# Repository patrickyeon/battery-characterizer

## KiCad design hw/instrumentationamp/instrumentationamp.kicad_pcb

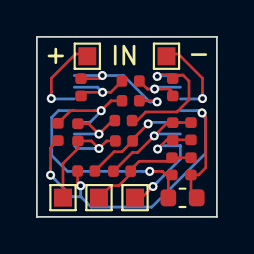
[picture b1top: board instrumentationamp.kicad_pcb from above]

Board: 2 copper layers, 10.0 x 10.0 mm, 21 parts (1 on the bottom side), 15 nets.

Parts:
C1: 100n; C_0603_1608Metric
C2: 10n; C_0402_1005Metric
R1, R4, R5, R11: 1K; R_0402_1005Metric
R2, R3: 2K; R_0402_1005Metric
R6, R7: 10K; R_0402_1005Metric
R8: DNI; R_0402_1005Metric
R9: 1M; R_0402_1005Metric
R10: 1k; R_0402_1005Metric
R12, R13: 250k; R_0402_1005Metric
TP1, TP2, TP3, TP4, TP7: Test_Point; TestPoint_Pad_1.0x1.0mm
U1: TLV274; TSSOP-14_4.4x5mm_P0.65mm

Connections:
/Vimeas: R7.1, R11.2, TP4.1, U1.1
/Vin+: TP2.1, U1.5
/Vin-: TP1.1, U1.10
/Viset: R8.1, R9.2, R10.1, TP3.1
/vout: C2.1, R13.1, TP7.1, U1.14
GND: C1.2, R6.2, R9.1, R12.1, U1.11
unnamed: C2.2, R10.2, R13.2, U1.13
unnamed: R1.1, R2.1, U1.9
unnamed: R1.2, R3.2, U1.6
unnamed: R2.2, R4.2, U1.8
unnamed: R3.1, R5.2, U1.7
unnamed: R4.1, R7.2, U1.2
unnamed: R5.1, R6.1, U1.3
unnamed: R11.1, R12.2, U1.12
VCC: C1.1, R8.2, U1.4

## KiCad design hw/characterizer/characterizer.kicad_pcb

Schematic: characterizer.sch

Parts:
C1: 1u; C_0603_1608Metric
C2: 470p; C_0603_1608Metric
C3: 2u2; C_0603_1608Metric
J1: 1988820; TERM_4_5mm; Digikey PN 277-1766-ND
R1: 0R; R_0603_1608Metric
R2: DNI; R_0603_1608Metric
R3, R4, R5: 10k; R_0603_1608Metric
U1: MIC5205-3.3; SOT-23-5; Digikey PN 576-1259-1-ND

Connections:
+3V3: C3.1, R5.1, U1.5 (OUT); also elsewhere on the board
+5V: R2.1; also elsewhere on the board
+6V: J1.1, J1.2, R1.1; also elsewhere on the board
/pairA/ADDR: R4.1; also elsewhere on the board
/pairB/ADDR: R5.2; also elsewhere on the board
GND: C1.2, C2.2, C3.2, J1.3, J1.4, R4.2, U1.2 (GND); also elsewhere on the board
unnamed: C1.1, R1.2, R2.2, R3.1, U1.1 (IN)
unnamed: C2.1, U1.4 (BP)
unnamed: R3.2, U1.3 (EN)

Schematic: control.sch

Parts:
C4: 4n7; C_0603_1608Metric
C5, C7, C9, C10, C11, C12, C13, C14: 100n; C_0603_1608Metric
C6, C8: 18p; C_0603_1608Metric
J2: Conn_02x05_Odd_Even; CONN_JTAG_10; Digikey PN 1175-1629-ND
J3: 10118194-0001LF; USB-microB-AMPH; Digikey PN 609-4618-1-ND
R6: 1M; R_0603_1608Metric
R7: DNI; R_0603_1608Metric
R8, R13, R14, R15, R16, R19, R20, R21, R22: 10k; R_0603_1608Metric
R9: 100k; R_0603_1608Metric
R10: 0; R_0603_1608Metric
R11, R12: 3k3; R_0603_1608Metric
R17, R18, R23, R24: 4k02; R_0603_1608Metric
U2: STM32F042K6T6; LQFP-32_7x7mm_P0.8mm; Digikey PN 497-14647-ND
U3: 74LVC2G04GW,125; SOT-363_SC-70-6; Digikey PN 1727-4032-1-ND
Y1: ABLS-8.000MHZ-B4-T; Crystal_SMD_HC49-SD; Digikey PN 535-10212-1-ND

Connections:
+3V3: C5.1, C7.1, C9.1, C10.1, J2.1, R7.1, R11.2, R12.2, U2.1, U2.5, U2.17, U3.5; also elsewhere on the board
+5V: R10.1; also elsewhere on the board
/SCL: R12.1, U2.19; also elsewhere on the board
/SDA: R11.1, U2.20; also elsewhere on the board
/mcu/CC_A: U2.6; also elsewhere on the board
/mcu/CC_B: U2.7; also elsewhere on the board
/mcu/CEN_A: U2.29; also elsewhere on the board
/mcu/CEN_B: U2.25; also elsewhere on the board
/mcu/DC_A: U2.8; also elsewhere on the board
/mcu/DC_B: U2.9; also elsewhere on the board
/mcu/ICHG_A: C14.1, R24.1; also elsewhere on the board
/mcu/ICHG_B: C12.1, R18.1; also elsewhere on the board
/mcu/IDCHG_A: C13.1, R23.1; also elsewhere on the board
/mcu/IDCHG_B: C11.1, R17.1; also elsewhere on the board
/mcu/VBAT0: R15.1; also elsewhere on the board
/mcu/VBAT1: R21.1; also elsewhere on the board
/mcu/VBAT2: R16.1; also elsewhere on the board
/mcu/VBAT3: R22.1; also elsewhere on the board
/pairA/DCHARGE: U2.30; also elsewhere on the board
/pairA/DIR: U2.18, U3.3; also elsewhere on the board
/pairA/nDIR: U3.4; also elsewhere on the board
/pairB/DCHARGE: R7.2, R8.1, U2.31; also elsewhere on the board
/pairB/DIR: U2.26, U3.1; also elsewhere on the board
/pairB/nDIR: U3.6; also elsewhere on the board
GND: C4.2, C5.2, C6.2, C7.2, C8.2, C9.2, C10.2, C11.2, C12.2, C13.2, C14.2, J2.3, J2.5, J2.9, J3.5, R6.1, R8.2, R9.1, R13.2, R14.2, R19.2, R20.2, U2.16, U2.32, U3.2; also elsewhere on the board
unnamed: C4.1, J3.6, J3.7, J3.8, J3.9, R6.2
unnamed: C6.1, U2.2, Y1.1
unnamed: C8.1, U2.3, Y1.2
unnamed: J2.2, U2.23
unnamed: J2.4, U2.24
unnamed: J2.10, U2.4
unnamed: J3.1, R10.2
unnamed: J3.2, U2.21
unnamed: J3.3, U2.22
unnamed: J3.4, R9.2
unnamed: R13.1, R15.2, U2.11
unnamed: R14.1, R16.2, U2.13
unnamed: R17.2, U2.15
unnamed: R18.2, U2.28
unnamed: R19.1, R21.2, U2.10
unnamed: R20.1, R22.2, U2.12
unnamed: R23.2, U2.14
unnamed: R24.2, U2.27

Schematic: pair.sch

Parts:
BT1, BT2: Battery_Cell; 18650-keyelco
C15, C16: 100n; C_0603_1608Metric
F1, F2: MF-USML700-2; R_1210_3225Metric; Digikey PN MF-USML700-2CT-ND
J4, J5, J6, J7: 36-54-ND; BATTERY_CLIP_36-54; Digikey PN 36-54-ND
R25, R26, R27, R28: 10k; R_0603_1608Metric
U4, U5: AT30TS74; MSOP-8_3x3mm_P0.65mm; Digikey PN 1611-AT30TS74-XM8M-B-ND

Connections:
+3V3: C15.1, C16.1, R26.1, U4.8, U5.8; also elsewhere on the board
/SCL: U4.2, U5.2; also elsewhere on the board
/SDA: U4.1, U5.1; also elsewhere on the board
/mcu/VBAT2: J4.1, J4.2, J4.3; also elsewhere on the board
/mcu/VBAT3: J6.1, J6.2, J6.3; also elsewhere on the board
/pairB/ADDR: U4.5, U5.5; also elsewhere on the board
GND: C15.2, C16.2, F1.2, F2.2, R25.2, R27.2, R28.2, U4.4, U5.4; also elsewhere on the board
unnamed: F1.1, J5.1, J5.2, J5.3
unnamed: F2.1, J7.1, J7.2, J7.3
unnamed: R25.1, U4.7
unnamed: R26.2, U5.7
unnamed: R27.1, U4.6
unnamed: R28.1, U5.6

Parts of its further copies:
BT3, BT4: Battery_Cell; 18650-keyelco
C32, C33: 100n; C_0603_1608Metric
F3, F4: MF-USML700-2; R_1210_3225Metric; Digikey PN MF-USML700-2CT-ND
J8, J9, J10, J11: 36-54-ND; BATTERY_CLIP_36-54; Digikey PN 36-54-ND
R62, R63, R64, R65: 10k; R_0603_1608Metric
U9, U10: AT30TS74; MSOP-8_3x3mm_P0.65mm; Digikey PN 1611-AT30TS74-XM8M-B-ND

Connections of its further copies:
+3V3: C32.1, C33.1, R63.1, U9.8, U10.8; also elsewhere on the board
/SCL: U9.2, U10.2; also elsewhere on the board
/SDA: U9.1, U10.1; also elsewhere on the board
/mcu/VBAT0: J8.1, J8.2, J8.3; also elsewhere on the board
/mcu/VBAT1: J10.1, J10.2, J10.3; also elsewhere on the board
/pairA/ADDR: U9.5, U10.5; also elsewhere on the board
GND: C32.2, C33.2, F3.2, F4.2, R62.2, R64.2, R65.2, U9.4, U10.4; also elsewhere on the board
unnamed: F3.1, J9.1, J9.2, J9.3
unnamed: F4.1, J11.1, J11.2, J11.3
unnamed: R62.1, U9.7
unnamed: R63.2, U10.7
unnamed: R64.1, U9.6
unnamed: R65.1, U10.6

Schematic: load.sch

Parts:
C17, C19: DNI; C_0603_1608Metric
C18: 100n; C_0603_1608Metric
Q1, Q2, Q6, Q8: BSS123; SOT-23; Digikey PN BSS123W-FDICT-ND
Q3, Q4, Q29, Q30: FDMA008P20LZ; MICROFET_2x2; Digikey PN FDMA008P20LZOSCT-ND
Q5: PSMN7R0-30MLC,115; LFPAK33; Digikey PN 1727-7144-1-ND
Q7: BSS84; SOT-23; Digikey PN BSS84W-FDICT-ND
R29, R30, R32, R34, R36: 3k3; R_0603_1608Metric
R31, R35: 20k; R_0603_1608Metric
R33: 0r01; R_2010_5025Metric; Digikey PN CSRN2010FK10L0CT-ND
R37: 2k; R_0603_1608Metric
R38, R41: 1k; R_0603_1608Metric
R39: 0; R_0603_1608Metric
R40, R42, R43: 10k; R_0603_1608Metric
TP1, TP2, TP3: Test_Point; PinHeader_1x01_P2.54mm_Vertical
U6: TLV272CS-13; MSOP-8_3x3mm_P0.65mm; Digikey PN TLV272IM8-13DICT-ND

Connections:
+6V: C18.2, R29.2, R30.2, R37.2, U6.8; also elsewhere on the board
/mcu/DC_B: R35.1, U6.1, U6.5; also elsewhere on the board
/mcu/IDCHG_B: R37.1, R38.2, U6.6; also elsewhere on the board
/mcu/VBAT2: Q29.S, Q29.S2; also elsewhere on the board
/mcu/VBAT3: Q30.S, Q30.S2; also elsewhere on the board
/pairB/DCHARGE: Q8.1, R43.1; also elsewhere on the board
/pairB/DIR: Q2.1; also elsewhere on the board
/pairB/nDIR: Q1.1; also elsewhere on the board
GND: C18.1, C19.1, Q1.2, Q2.2, Q5.1, Q5.2, Q5.3, Q6.2, Q8.2, R31.2, R38.1, R40.2, R43.2, U6.4; also elsewhere on the board
unnamed: C17.1, Q5.4, R36.2, R39.2
unnamed: C17.2, Q5.5, R33.1, R34.1, R36.1
unnamed: C19.2, Q7.2, R41.1, R42.1
unnamed: Q1.3, Q3.G, Q29.G, R29.1
unnamed: Q2.3, Q4.G, Q30.G, R30.1
unnamed: Q3.S, Q3.S2, Q4.S, Q4.S2, R32.1, R33.2
unnamed: Q6.1, Q7.3, R40.1
unnamed: Q6.3, R39.1
unnamed: Q7.1, Q8.3, R42.2
unnamed: Q3.D, Q29.D
unnamed: Q4.D, Q30.D
unnamed: R31.1, R32.2, U6.3
unnamed: R34.2, R35.2, U6.2
unnamed: R41.2, U6.7

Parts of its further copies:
C34, C36: DNI; C_0603_1608Metric
C35: 100n; C_0603_1608Metric
Q15, Q16, Q20, Q22: BSS123; SOT-23; Digikey PN BSS123W-FDICT-ND
Q17, Q18, Q33, Q34: FDMA008P20LZ; MICROFET_2x2; Digikey PN FDMA008P20LZOSCT-ND
Q19: PSMN7R0-30MLC,115; LFPAK33; Digikey PN 1727-7144-1-ND
Q21: BSS84; SOT-23; Digikey PN BSS84W-FDICT-ND
R66, R67, R69, R71, R73: 3k3; R_0603_1608Metric
R68, R72: 20k; R_0603_1608Metric
R70: 0r01; R_2010_5025Metric; Digikey PN CSRN2010FK10L0CT-ND
R74: 2k; R_0603_1608Metric
R75, R78: 1k; R_0603_1608Metric
R76: 0; R_0603_1608Metric
R77, R79, R80: 10k; R_0603_1608Metric
TP7, TP8, TP9: Test_Point; PinHeader_1x01_P2.54mm_Vertical
U11: TLV272CS-13; MSOP-8_3x3mm_P0.65mm; Digikey PN TLV272IM8-13DICT-ND

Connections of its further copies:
+6V: C35.2, R66.2, R67.2, R74.2, U11.8; also elsewhere on the board
/mcu/DC_A: R72.1, U11.1, U11.5; also elsewhere on the board
/mcu/IDCHG_A: R74.1, R75.2, U11.6; also elsewhere on the board
/mcu/VBAT0: Q33.S, Q33.S2; also elsewhere on the board
/mcu/VBAT1: Q34.S, Q34.S2; also elsewhere on the board
/pairA/DCHARGE: Q22.1, R80.1; also elsewhere on the board
/pairA/DIR: Q16.1; also elsewhere on the board
/pairA/nDIR: Q15.1; also elsewhere on the board
GND: C35.1, C36.1, Q15.2, Q16.2, Q19.1, Q19.2, Q19.3, Q20.2, Q22.2, R68.2, R75.1, R77.2, R80.2, U11.4; also elsewhere on the board
unnamed: C34.1, Q19.4, R73.2, R76.2
unnamed: C34.2, Q19.5, R70.1, R71.1, R73.1
unnamed: C36.2, Q21.2, R78.1, R79.1
unnamed: Q15.3, Q17.G, Q33.G, R66.1
unnamed: Q16.3, Q18.G, Q34.G, R67.1
unnamed: Q17.D, Q33.D
unnamed: Q17.S, Q17.S2, Q18.S, Q18.S2, R69.1, R70.2
unnamed: Q18.D, Q34.D
unnamed: Q20.1, Q21.3, R77.1
unnamed: Q20.3, R76.1
unnamed: Q21.1, Q22.3, R79.2
unnamed: R68.1, R69.2, U11.3
unnamed: R71.2, R72.2, U11.2
unnamed: R78.2, U11.7

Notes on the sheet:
30W here

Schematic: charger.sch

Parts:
C20: 10n; C_0603_1608Metric
C21, C22, C23, C28: 10u; C_1206_3216Metric; Digikey PN 311-1376-1-ND
C24: 63p4; C_0603_1608Metric
C25, C27, C30: 100n; C_0603_1608Metric
C26: 1n91; C_0603_1608Metric
C29, C31: DNI; C_0603_1608Metric
L1: 2.2uH; IND-10.4x10.4; Digikey PN 495-1799-1-ND
Q9, Q10, Q14: BSS123; SOT-23; Digikey PN BSS123W-FDICT-ND
Q11, Q12, Q31, Q32: FDMA008P20LZ; MICROFET_2x2; Digikey PN FDMA008P20LZOSCT-ND
Q13: BSS84; SOT-23; Digikey PN BSS84W-FDICT-ND
R44, R46, R47, R50, R52, R56, R60: 3k3; R_0603_1608Metric
R45: 78k7; R_0603_1608Metric
R48: 2k61; R_0603_1608Metric
R49, R55: 20k; R_0603_1608Metric
R51: 0r01; R_2010_5025Metric; Digikey PN CSRN2010FK10L0CT-ND
R53: 86k6; R_0603_1608Metric
R54: 14k3; R_0603_1608Metric
R57: 2k; R_0603_1608Metric
R58: 1k; R_0603_1608Metric
R59, R61: 0; R_0603_1608Metric
TP4, TP5, TP6: Test_Point; PinHeader_1x01_P2.54mm_Vertical
U7: TPS54719; WQFN-16-1EP_3x3mm_P0.5mm_EP1.75x1.75mm; Digikey PN 296-36812-1-ND
U8: TLV272CS-13; MSOP-8_3x3mm_P0.65mm; Digikey PN TLV272IM8-13DICT-ND

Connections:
+6V: C21.1, C22.1, C23.1, C25.2, C30.2, R44.1, R46.1, R47.2, R57.2, U7.1, U7.2, U7.16, U8.8; also elsewhere on the board
/mcu/CC_B: R55.1, U8.1, U8.5; also elsewhere on the board
/mcu/CEN_B: U7.15; also elsewhere on the board
/mcu/ICHG_B: R57.1, R58.2, U8.6; also elsewhere on the board
/mcu/VBAT2: Q31.S, Q31.S2; also elsewhere on the board
/mcu/VBAT3: Q32.S, Q32.S2; also elsewhere on the board
/pairB/DIR: Q9.1; also elsewhere on the board
/pairB/nDIR: Q10.1; also elsewhere on the board
/pairB/sheet5BBBF842/Vbatt: C29.1, Q11.S, Q11.S2, Q12.S, Q12.S2, Q13.2, R51.1, R52.1, R53.1, R56.1
/pairB/sheet5BBBF842/Vsens: Q13.3, R53.2, R54.1, U7.6
GND: C20.2, C21.2, C22.2, C23.2, C24.2, C25.1, C26.2, C28.2, C30.1, C31.2, Q9.2, Q10.2, Q14.2, R45.2, R49.2, R54.2, R58.1, R60.2, U7.3, U7.4, U7.5, U7.17, U8.4; also elsewhere on the board
unnamed: C20.1, U7.9
unnamed: C24.1, R48.1, U7.7
unnamed: C26.1, R48.2
unnamed: C27.1, L1.1, U7.10, U7.11, U7.12
unnamed: C27.2, U7.13
unnamed: C28.1, L1.2, R50.1, R51.2
unnamed: C29.2, Q13.1, R56.2, R59.2
unnamed: C31.1, Q14.1, R60.1, R61.2
unnamed: Q10.3, Q12.G, Q32.G, R47.1
unnamed: Q11.D, Q31.D
unnamed: Q9.3, Q11.G, Q31.G, R46.2
unnamed: Q12.D, Q32.D
unnamed: Q14.3, R59.1
unnamed: R44.2, U7.14
unnamed: R45.1, U7.8
unnamed: R49.1, R50.2, U8.3
unnamed: R52.2, R55.2, U8.2
unnamed: R61.1, U8.7

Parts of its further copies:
C37: 10n; C_0603_1608Metric
C38, C39, C40, C45: 10u; C_1206_3216Metric; Digikey PN 311-1376-1-ND
C41: 63p4; C_0603_1608Metric
C42, C44, C47: 100n; C_0603_1608Metric
C43: 1n91; C_0603_1608Metric
C46, C48: DNI; C_0603_1608Metric
L2: 2.2uH; IND-10.4x10.4; Digikey PN 495-1799-1-ND
Q23, Q24, Q28: BSS123; SOT-23; Digikey PN BSS123W-FDICT-ND
Q25, Q26, Q35, Q36: FDMA008P20LZ; MICROFET_2x2; Digikey PN FDMA008P20LZOSCT-ND
Q27: BSS84; SOT-23; Digikey PN BSS84W-FDICT-ND
R81, R83, R84, R87, R89, R93, R97: 3k3; R_0603_1608Metric
R82: 78k7; R_0603_1608Metric
R85: 2k61; R_0603_1608Metric
R86, R92: 20k; R_0603_1608Metric
R88: 0r01; R_2010_5025Metric; Digikey PN CSRN2010FK10L0CT-ND
R90: 86k6; R_0603_1608Metric
R91: 14k3; R_0603_1608Metric
R94: 2k; R_0603_1608Metric
R95: 1k; R_0603_1608Metric
R96, R98: 0; R_0603_1608Metric
TP10, TP11, TP12: Test_Point; PinHeader_1x01_P2.54mm_Vertical
U12: TPS54719; WQFN-16-1EP_3x3mm_P0.5mm_EP1.75x1.75mm; Digikey PN 296-36812-1-ND
U13: TLV272CS-13; MSOP-8_3x3mm_P0.65mm; Digikey PN TLV272IM8-13DICT-ND

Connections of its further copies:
+6V: C38.1, C39.1, C40.1, C42.2, C47.2, R81.1, R83.1, R84.2, R94.2, U12.1, U12.2, U12.16, U13.8; also elsewhere on the board
/mcu/CC_A: R92.1, U13.1, U13.5; also elsewhere on the board
/mcu/CEN_A: U12.15; also elsewhere on the board
/mcu/ICHG_A: R94.1, R95.2, U13.6; also elsewhere on the board
/mcu/VBAT0: Q35.S, Q35.S2; also elsewhere on the board
/mcu/VBAT1: Q36.S, Q36.S2; also elsewhere on the board
/pairA/DIR: Q23.1; also elsewhere on the board
/pairA/nDIR: Q24.1; also elsewhere on the board
/pairA/sheet5BBBF842/Vbatt: C46.1, Q25.S, Q25.S2, Q26.S, Q26.S2, Q27.2, R88.1, R89.1, R90.1, R93.1
/pairA/sheet5BBBF842/Vsens: Q27.3, R90.2, R91.1, U12.6
GND: C37.2, C38.2, C39.2, C40.2, C41.2, C42.1, C43.2, C45.2, C47.1, C48.2, Q23.2, Q24.2, Q28.2, R82.2, R86.2, R91.2, R95.1, R97.2, U12.3, U12.4, U12.5, U12.17, U13.4; also elsewhere on the board
unnamed: C37.1, U12.9
unnamed: C41.1, R85.1, U12.7
unnamed: C43.1, R85.2
unnamed: C44.1, L2.1, U12.10, U12.11, U12.12
unnamed: C44.2, U12.13
unnamed: C45.1, L2.2, R87.1, R88.2
unnamed: C46.2, Q27.1, R93.2, R96.2
unnamed: C48.1, Q28.1, R97.1, R98.2
unnamed: Q23.3, Q25.G, Q35.G, R83.2
unnamed: Q24.3, Q26.G, Q36.G, R84.1
unnamed: Q25.D, Q35.D
unnamed: Q26.D, Q36.D
unnamed: Q28.3, R96.1
unnamed: R81.2, U12.14
unnamed: R82.1, U12.8
unnamed: R86.1, R87.2, U13.3
unnamed: R89.2, R92.2, U13.2
unnamed: R98.1, U13.7

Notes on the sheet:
internally pulled up
500kHz
4.125u after DC bias (tool suggested CC0603MRX5R5BB106)
10u total, after DC bias effect

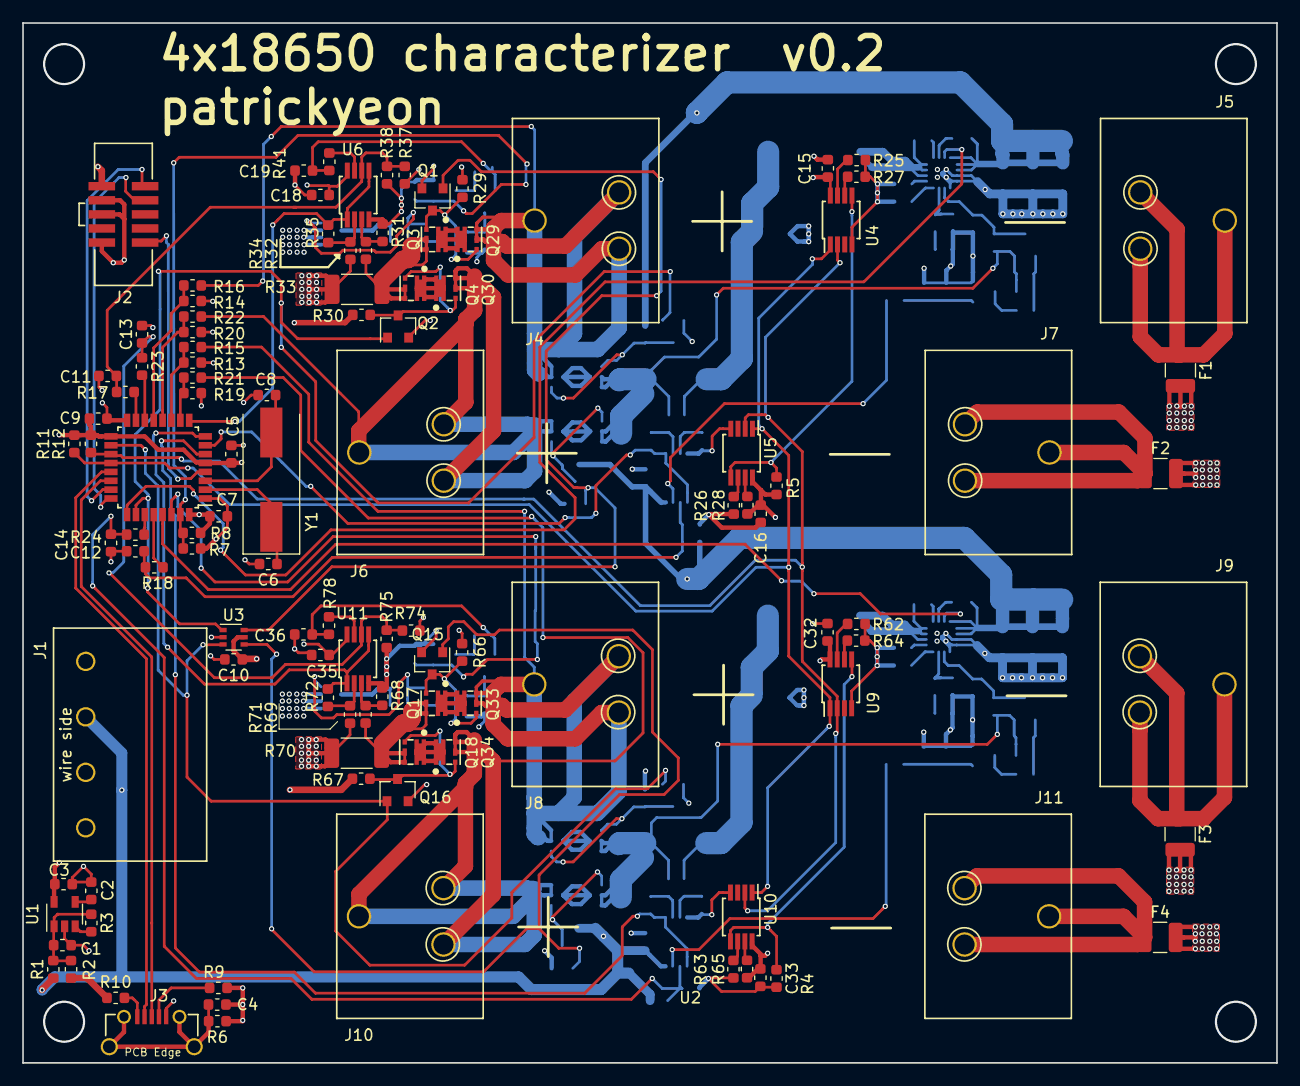
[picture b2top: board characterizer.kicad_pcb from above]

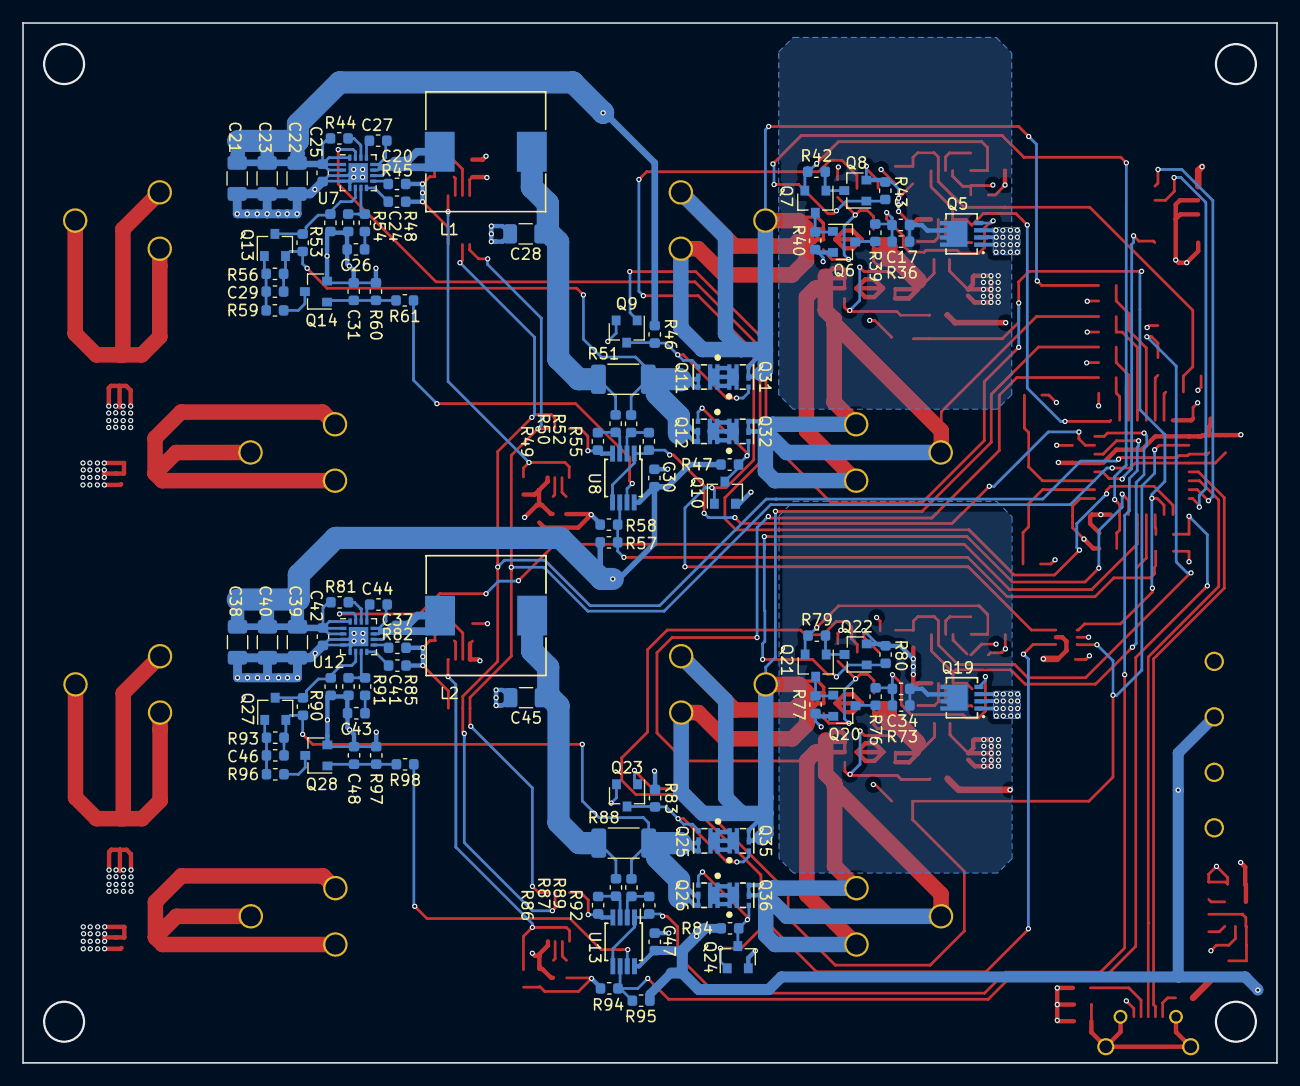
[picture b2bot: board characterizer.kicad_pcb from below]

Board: 4 copper layers, 113.0 x 93.7 mm, 217 parts (102 on the bottom side), 129 nets.

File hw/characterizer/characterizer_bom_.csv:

Component,Description,Part,References,Value,Footprint,Quantity Per PCB,Datasheet,Digikey PN
1,single battery cell,Battery_Cell,BT1 BT2 BT3 BT4,Battery_Cell,18650-keyelco,4,~,
2,Unpolarized capacitor,C_Small,C5 C7 C9 C10 C11 C12 C13 C14 C15 C16 C18 C25 C27 C30 C32 C33 C35 C42 C44 C47,100n,C_0603_1608Metric,20,~,
3,Unpolarized capacitor,C_Small,C20 C37,10n,C_0603_1608Metric,2,~,
4,Unpolarized capacitor,C_Small,C21 C22 C23 C28 C38 C39 C40 C45,10u,C_1206_3216Metric,8,~,311-1376-1-ND
5,Unpolarized capacitor,C_Small,C6 C8,18p,C_0603_1608Metric,2,~,
6,Unpolarized capacitor,C_Small,C26 C43,1n91,C_0603_1608Metric,2,~,
7,Unpolarized capacitor,C_Small,C1,1u,C_0603_1608Metric,1,~,
8,Unpolarized capacitor,C_Small,C3,2u2,C_0603_1608Metric,1,~,
9,Unpolarized capacitor,C_Small,C2,470p,C_0603_1608Metric,1,~,
10,Unpolarized capacitor,C_Small,C4,4n7,C_0603_1608Metric,1,~,
11,Unpolarized capacitor,C_Small,C24 C41,63p4,C_0603_1608Metric,2,~,
12,Unpolarized capacitor,C_Small,C17 C19 C29 C31 C34 C36 C46 C48,DNI,C_0603_1608Metric,8,~,
13,"resettable fuse, polymeric positive temperature coefficient (PPTC), small symbol",Polyfuse_Small,F1 F2 F3 F4,MF-USML700-2,R_1210_3225Metric,4,~,MF-USML700-2CT-ND
14,,USB_OTG,J3,10118194-0001LF,USB-microB-AMPH,1, ~,609-4618-1-ND
15,"Generic screw terminal, single row, 01x04, script generated (kicad-library-utils/schlib/autogen/connector/)",Screw_Terminal_01x04,J1,1988820,TERM_4_5mm,1,~,277-1766-ND
16,"Generic connector, single row, 01x03, script generated (kicad-library-utils/schlib/autogen/connector/)",Conn_01x03,J4 J5 J6 J7 J8 J9 J10 J11,36-54-ND,BATTERY_CLIP_36-54,8,~,36-54-ND
17,"Generic connector, double row, 02x05, odd/even pin numbering scheme (row 1 odd numbers, row 2 even numbers), script generated (kicad-library-utils/schlib/autogen/connector/)",Conn_02x05_Odd_Even,J2,Conn_02x05_Odd_Even,CONN_JTAG_10,1,~,1175-1629-ND
18,"Inductor, small symbol",L_Small,L1 L2,2.2uH,IND-10.4x10.4,2,~,495-1799-1-ND
19,Transistor N-MOSFETwith substrate diode (general),Q_NMOS_GSD,Q1 Q2 Q6 Q8 Q9 Q10 Q14 Q15 Q16 Q20 Q22 Q23 Q24 Q28,BSS123,SOT-23,14,~,BSS123W-FDICT-ND
20,Transistor P-MOSFET with substrate diode (general),Q_PMOS_GSD,Q7 Q13 Q21 Q27,BSS84,SOT-23,4,~,BSS84W-FDICT-ND
21,,FDMA008P20LZ,Q3 Q4 Q11 Q12 Q17 Q18 Q25 Q26 Q29 Q30 Q31 Q32 Q33 Q34 Q35 Q36,FDMA008P20LZ,MICROFET_2x2,16,~,FDMA008P20LZOSCT-ND
22,,PSMN7R0-30MLC,Q5 Q19,"PSMN7R0-30MLC,115",LFPAK33,2,~,1727-7144-1-ND
23,"Resistor, small symbol",R_Small,R1 R10 R39 R59 R61 R76 R96 R98,0R,R_0603_1608Metric,8,~,
24,"Resistor, small symbol",R_Small,R33 R51 R70 R88,0r01,R_2010_5025Metric,4,~,CSRN2010FK10L0CT-ND
25,"Resistor, small symbol",R_Small,R9,100k,R_0603_1608Metric,1,~,
26,"Resistor, small symbol",R_Small,R3 R4 R5 R8 R13 R14 R15 R16 R19 R20 R21 R22 R25 R26 R27 R28 R40 R42 R43 R62 R63 R64 R65 R77 R79 R80,10k,R_0603_1608Metric,26,~,
27,"Resistor, small symbol",R_Small,R54 R91,14k3,R_0603_1608Metric,2,~,
28,"Resistor, small symbol",R_Small,R6,1M,R_0603_1608Metric,1,~,
29,"Resistor, small symbol",R_Small,R38 R41 R58 R75 R78 R95,1k,R_0603_1608Metric,6,~,
30,"Resistor, small symbol",R_Small,R31 R35 R49 R55 R68 R72 R86 R92,20k,R_0603_1608Metric,8,~,
31,"Resistor, small symbol",R_Small,R37 R57 R74 R94,2k,R_0603_1608Metric,4,~,
32,"Resistor, small symbol",R_Small,R48 R85,2k61,R_0603_1608Metric,2,~,
33,"Resistor, small symbol",R_Small,R11 R12 R29 R30 R32 R34 R36 R44 R46 R47 R50 R52 R56 R60 R66 R67 R69 R71 R73 R81 R83 R84 R87 R89 R93 R97,3k3,R_0603_1608Metric,26,~,
34,"Resistor, small symbol",R_Small,R17 R18 R23 R24,4k02,R_0603_1608Metric,4,~,
35,"Resistor, small symbol",R_Small,R45 R82,78k7,R_0603_1608Metric,2,~,
36,"Resistor, small symbol",R_Small,R53 R90,86k6,R_0603_1608Metric,2,~,
37,"Resistor, small symbol",R_Small,R2 R7,DNI,R_0603_1608Metric,2,~,
38,,"74LVC2G04GW,125",U3,"74LVC2G04GW,125",SOT-363_SC-70-6,1,,1727-4032-1-ND
39,,AT30TS74,U4 U5 U9 U10,AT30TS74,MSOP-8_3x3mm_P0.65mm,4,,1611-AT30TS74-XM8M-B-ND
40,"150mA Low Dropout Voltage Regulator, Fixed Output 3.3V, SOT-23-5",MIC5205-3.3,U1,MIC5205-3.3,SOT-23-5,1,http://ww1.microchip.com/downloads/en/devicedoc/mic5205.pdf,576-1259-1-ND
41,,STM32F042K6T6,U2,STM32F042K6T6,LQFP-32_7x7mm_P0.8mm,1,,497-14647-ND
42,"Dual Opamp, SOIC-8/DIP-8/SSOP-8/TO-99",Opamp_Dual_Generic,U6 U8 U11 U13,TLV272CS-13,MSOP-8_3x3mm_P0.65mm,4,,TLV272CS-13DICT-ND
43,,TPS54719,U7 U12,TPS54719,WQFN-16-1EP_3x3mm_P0.5mm_EP1.75x1.75mm,2,,296-36812-1-ND
44,Two pin crystal,Crystal,Y1,ABLS-8.000MHZ-B4-T,Crystal_SMD_HC49-SD,1,~,535-10212-1-ND





Component Groups:,44
Component Count:,217
Fitted Components:,217
Number of PCBs:,1
Total components:,217
Schematic Version:,
Schematic Date:,
BoM Date:,Fri 28 Sep 2018 05:45:31 PM PDT
Schematic Source:,/home/pat/projects/batteries/hw/characterizer/characterizer.sch
KiCad Version:,Eeschema 5.0.0-fee4fd1~65~ubuntu17.10.1

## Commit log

2018-09-19 initial schematic, start layout
2018-09-24 layout functionally complete
2018-09-25 layout as-ordered
2018-09-25 infrastructure for firmware dev (copied from hackhat)
2018-09-27 well, start of charge 'director', and required testing framework
2018-09-27 direction switching implemented
2018-09-28 basic cell voltage checking before starting charge/discharge
2018-09-28 updated makefile to build drivers too
2018-09-28 small layout fix
2018-09-28 WAG at an ADC driver
2018-09-28 very rudimentary scheduler
2018-09-28 very simple driver for AT30TS74
2018-09-28 director_checkup for an in-progress charge/discharge cycle
2018-09-29 updating schematic with digikey pns
2018-10-01 working on being able to log stats/telemetry
2018-10-01 can log on multiple pages of flash now
2018-10-02 can log on multiple pages, better now
2018-10-04 logger_init and logger_write are started
2018-10-04 write and read lines is okay ish
2018-10-04 now we can write across many pages, error on overflow
2018-10-04 stricter compiler settings, and fixing them
2018-10-05 for the easiest case, we can now dequeue from log
2018-10-06 dequeueing properly frees up space
2018-10-06 adding the bulk of the log message types
2018-10-06 a bit of logger cleanup
2018-10-09 USB driver brought in, start of command handler
2018-10-09 a bit smoother recovery for garbage on the line
2018-10-09 slightly more flexible command handling
2018-10-09 time setting over command channel
2018-10-11 real flash addresses for the log now
2018-10-11 spaces not tabs
2018-10-11 explicit pointer conversions
2018-10-12 flash implementation, works as tested on real hardware
2018-10-15 adjusting logging/flash to deal with how the stm works
2018-10-15 well I've started building for the target
2018-10-16 small board fixes
2018-10-17 i2c temp sensors confirmed working
2018-10-17 ADC works, needs to be prettier
2018-10-19 adding tick/tock timing capability
2018-10-19 ugly, but more functional flash management
2018-10-23 quieter make test
2018-10-23 a PWM that works at least
2018-10-23 log current, voltage not as adc codes
2018-10-23 yet better test reporting output
2018-10-23 proper use of PWM outputs for current setting
2018-10-24 made a tiny instrumentation amplifier board to cover for a mistake on the design
2018-10-31 fix pwm output mapping
2018-10-31 part number for instrumentation amp
2018-10-31 discharge current control with pwm spice sim
2018-11-05 some more ltspice simulations
2018-11-05 add DIRECTOR_UNSAFE mode
2018-11-05 quick notes on making flash work
2018-11-05 updated schematics with all the mods so far
2018-11-06 logging moved into director.c, untested though
2018-11-06 tick/tock confirmed working
2018-11-08 first stab at host-side code, not fully tested, but eventually can share command listing
2018-11-08 two timers for two indep. tick/tock
2018-11-08 comms.py works better thanks to some testing
2018-11-08 removing debug stuff
2018-11-08 bugfix for reading ADC
2018-11-09 big messages (commands) revamp
    * `commands` are now `messages`
    * host code very adaptable to changes in msg_def.json
    * number of conveniences in host code
    * eliminating ACKs, more strict with message construction
2018-11-09 janky initial C codegen
2018-11-09 bringing tests up to date with code changes
2018-11-09 small re-org on comms.py, now claim exclusive use of serial device
2018-11-11 letting the director manage config stuff
2018-11-11 just a couple more things for standard build
2018-11-11 remove redundant gpio setup
2018-11-12 i2c timeouts and nacks handled. not great, but not horrible
2018-11-12 a bit more helpful Makefile, msg_def tweak
2018-11-12 updating tests to track code changes
2018-11-12 logging update
    * actually return timestamps
    * log at more predictable times in director_tick
2018-11-13 Makefile treat generated files properly
2018-11-13 adding a watchdog timer
2018-11-13 time sync and log dumping added
2018-11-13 proper Viset and final stage on instrumentation amp
2018-11-25 reworking i2c timeouts so that it doesn't bog down when nothing is on the bus
2018-11-25 I2C working and at 1MHz
2018-11-25 monitoring timings on i2c
2018-11-25 whoops, clean up i2c errors
2018-11-26 updated to make the tests pass again
2018-11-26 writeup from i2c adventures
2018-12-07 ADC has averaging, internal vref, and temperature
